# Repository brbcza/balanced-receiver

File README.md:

# Balanced Audio Receiver

The **Balanced Audio Receiver** is a versatile, compact PCB (Printed Circuit Board) designed for DIY audio enthusiasts, particularly for use as an input stage in custom speaker projects. The design integrates a balanced XLR 3-pin input and includes an onboard 5V buck converter to provide power for additional components, making it a comprehensive solution for audio applications that require both signal processing and power management.

This board is ideal for anyone looking to build high-quality audio systems, such as home audio setups or custom speaker projects, with a focus on clean, balanced audio signal processing.

> [!NOTE]  
> The latest production files for the Balanced Audio Receiver can be downloaded from the [latest release](https://github.com/brbcza/balanced-receiver/releases/latest).  
> The [Interactive BOM](https://brbcza.github.io/balanced-receiver/balanced-receiver_ibom.html) is also available in the latest release for easier component sourcing.

## Key Futures

The Balanced Audio Receiver board incorporates several essential features to ensure high performance and flexibility:

* Fully balanced XLR input
* Diferencial THAT1240 amplifier to process incoming audio signal
* Integrated 5V buck converter to power onboard ICs and additional external electronics
* Integraded charge pump to generate -5V to power signal amplifier
* Optional 5V output to power external FAN

## Board Design and Component Sourcing

The Balanced Audio Receiver PCB is designed to be as modular and flexible as possible. It is intended for use in various custom audio systems where space, signal integrity, and power efficiency are important considerations. The generated [Bill of Materials](https://github.com/brbcza/balanced-receiver/releases/latest) from latest release will help to guide you in sourcing the components for assembly.

> **Interactive BOM**  
> The interactive BOM can be found at the following link: [Interactive BOM](https://brbcza.github.io/balanced-receiver/balanced-receiver_ibom.html).

## Contributing

I welcome any contributions to the project. If you have suggestions for improvements, bug fixes, or want to add new features, feel free to submit pull requests or open issues.

## License

The Balanced Audio Receiver is open-source hardware, licensed under the [GPLv3 License](LICENSE). Feel free to modify and adapt the design for your own use, but please attribute the original project if you distribute it.

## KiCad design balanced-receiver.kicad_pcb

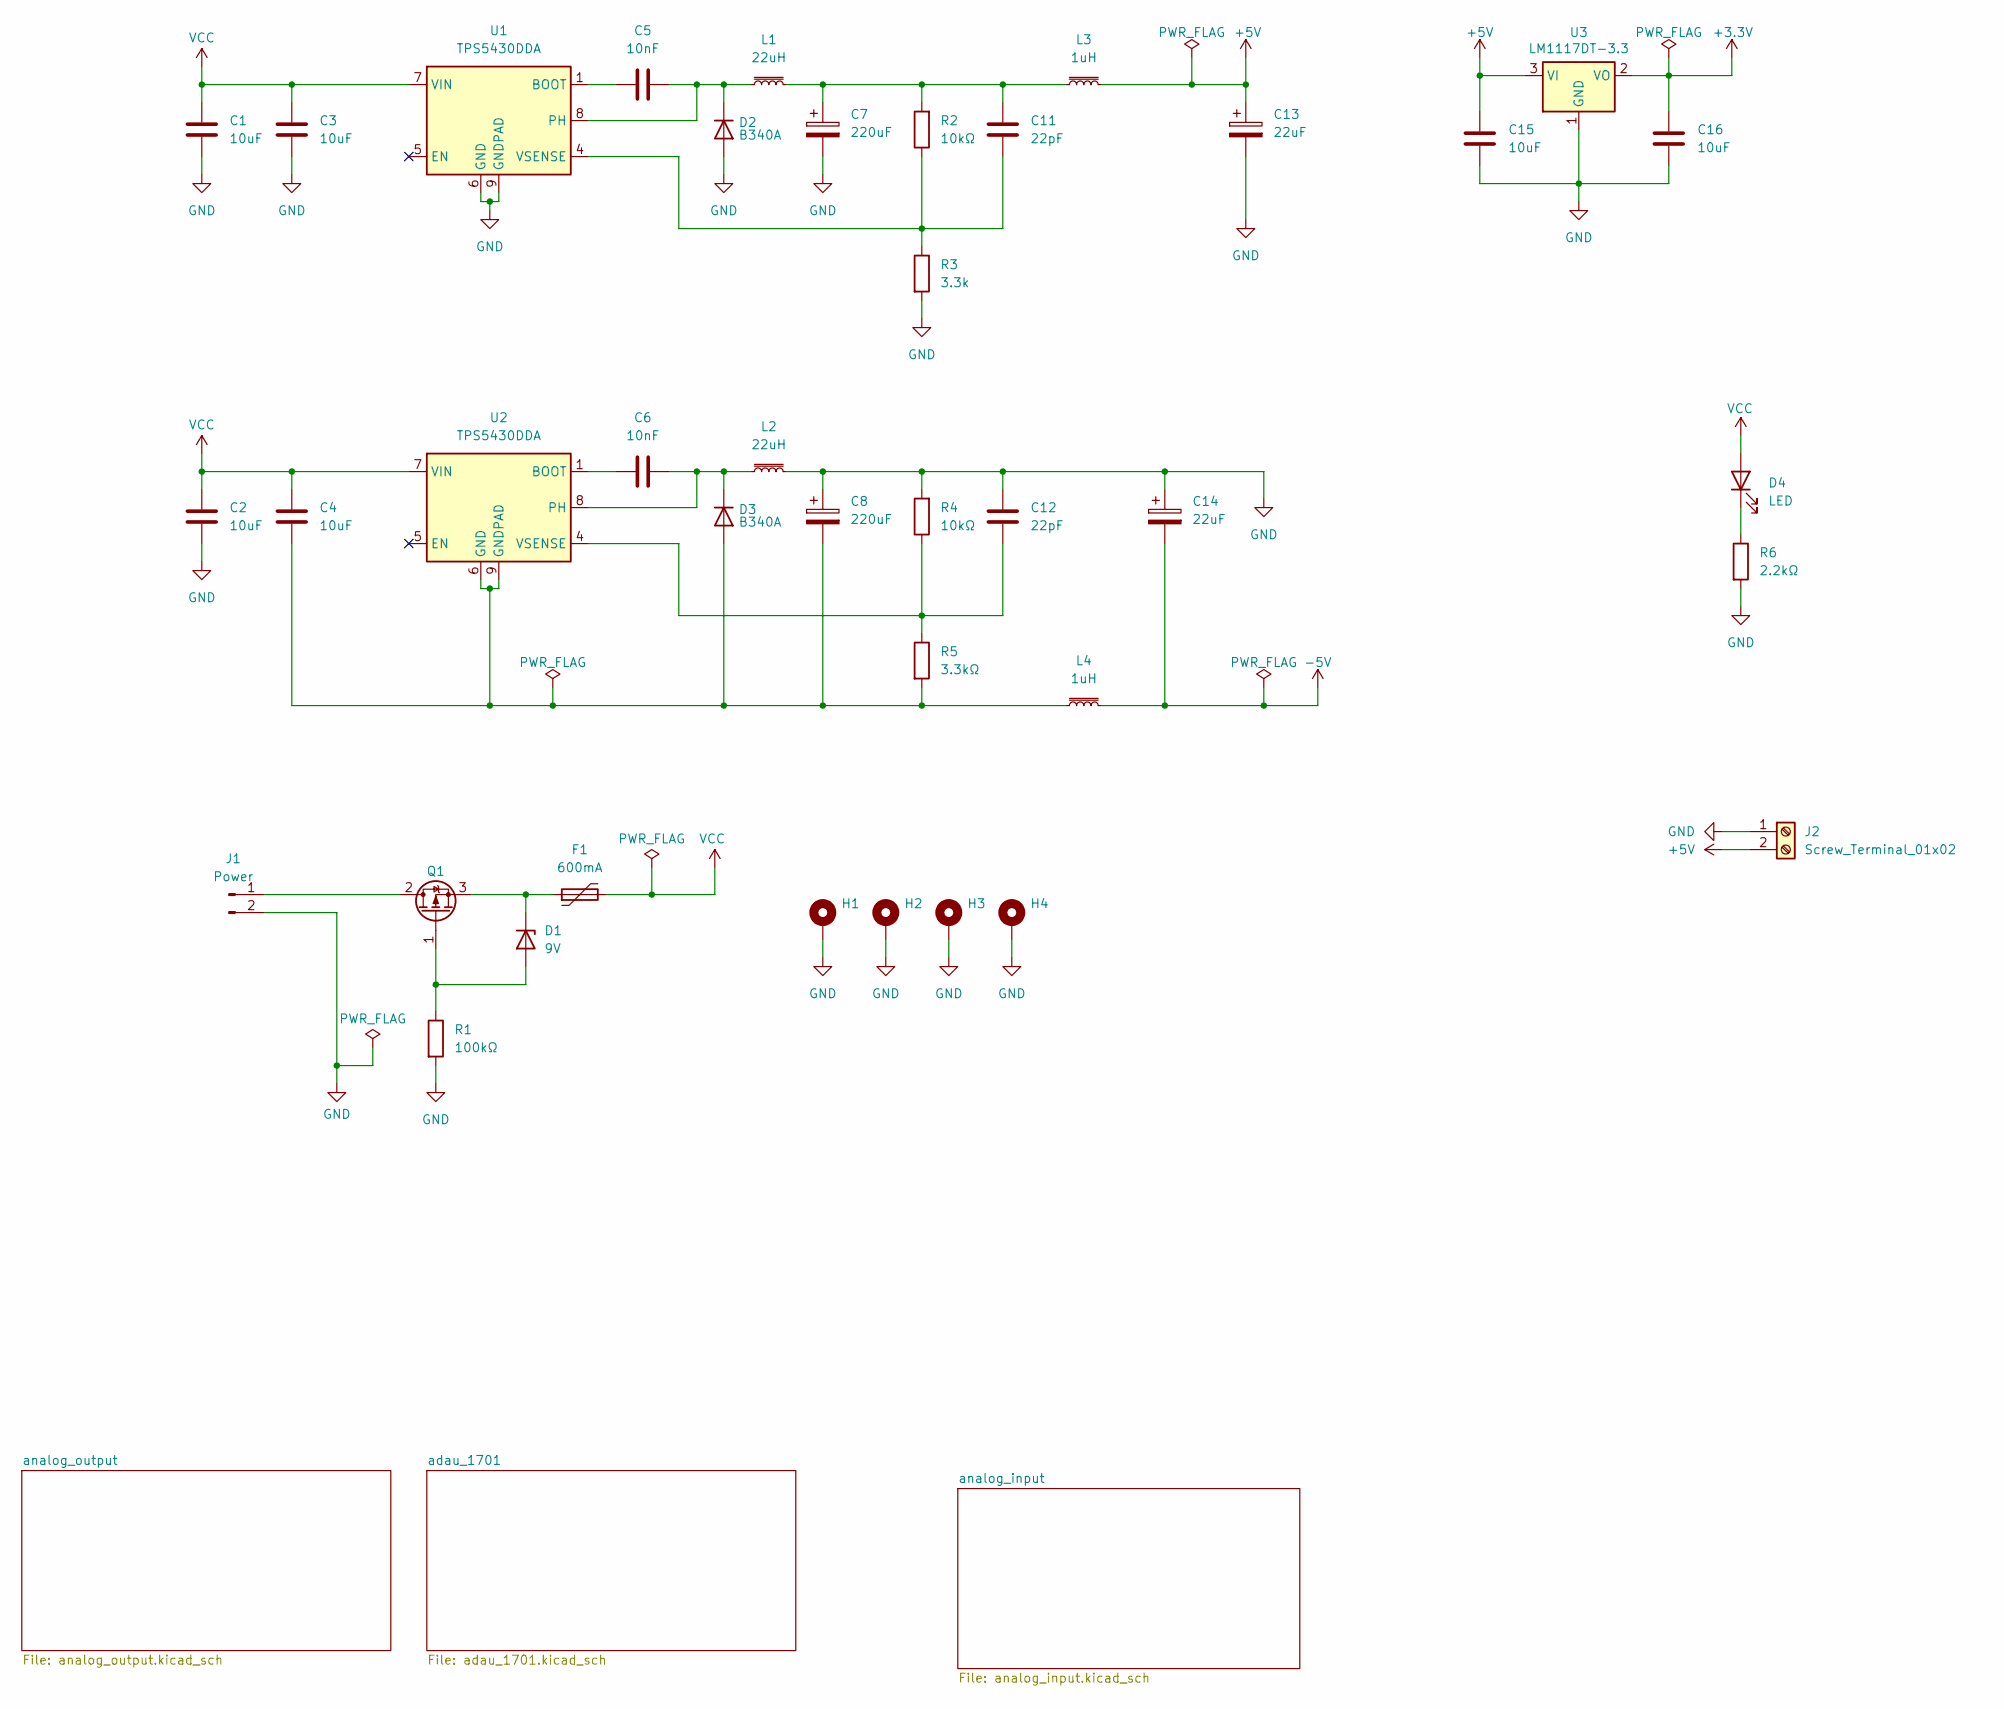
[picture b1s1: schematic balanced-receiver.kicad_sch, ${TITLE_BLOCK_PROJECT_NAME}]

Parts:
C1, C2, C3, C4, C15, C16: 10uF; C_0805_2012Metric_Pad1.18x1.45mm_HandSolder
C5, C6: 10nF; C_0805_2012Metric_Pad1.18x1.45mm_HandSolder
C7, C8: 220uF; CP_Elec_6.3x7.7
C11, C12: 22pF; C_0805_2012Metric_Pad1.18x1.45mm_HandSolder
C13, C14: 22uF; CP_Elec_4x5.4
D1: 9V; D_SOD-123; LCSC C5182291
D2, D3: B340A; D_SMA_Handsoldering
D4: LED; LED_0805_2012Metric_Pad1.15x1.40mm_HandSolder
F1: 600mA; Fuse_1812_4532Metric_Pad1.30x3.40mm_HandSolder; LCSC C135357
H1, H2, H3, H4: MountingHole_Pad_MP; MountingHole_2.2mm_M2_DIN965_Pad_TopBottom
J1: Power; JST_XH_B2B-XH-A_1x02_P2.50mm_Vertical
J2: Screw_Terminal_01x02; JST_XH_B2B-XH-AM_1x02_P2.50mm_Vertical
L1, L2: 22uH; L_APV_ANR6028
L3, L4: 1uH; L_APV_APH0420
Q1: Q_PMOS_GDS; SOT-223-3_TabPin2; LCSC SOT-23
R1: 100kΩ; R_0805_2012Metric_Pad1.20x1.40mm_HandSolder
R2, R4: 10kΩ; R_0805_2012Metric_Pad1.20x1.40mm_HandSolder
R3: 3.3k; R_0805_2012Metric_Pad1.20x1.40mm_HandSolder
R5: 3.3kΩ; R_0805_2012Metric_Pad1.20x1.40mm_HandSolder
R6: 2.2kΩ; R_0805_2012Metric_Pad1.20x1.40mm_HandSolder
U1, U2: TPS5430DDA; TI_SO-PowerPAD-8
U3: LM1117DT-3.3; SOT-223-3_TabPin2

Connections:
+3.3V: C16.2, U3.2 (VO); also elsewhere on the board
+5V: C13.1, C15.2, J2.2, L3.2, U3.3 (VI); also elsewhere on the board
-5V: C14.2, L4.2; also elsewhere on the board
GND: C1.2, C2.2, C3.2, C7.2, C8.1, C12.1, C13.2, C14.1, C15.1, C16.1, D2.2 (A), H1.MP, H2.MP, H3.MP, H4.MP, J1.2, J2.1, L2.2, R1.2, R3.2, R4.2, R6.2, U1.6 (GND), U1.9 (GNDPAD), U3.1 (GND); also elsewhere on the board
unnamed: C7.1, C11.1, L1.2, L3.1, R2.2
unnamed: D1.2 (A), Q1.1 (G), R1.1
unnamed: D1.1 (K), F1.1, Q1.3 (S)
unnamed: C5.2, D2.1 (K), L1.1, U1.8 (PH)
unnamed: C4.2, C8.2, D3.2 (A), L4.1, R5.2, U2.6 (GND), U2.9 (GNDPAD)
unnamed: C6.2, D3.1 (K), L2.1, U2.8 (PH)
unnamed: D4.1 (K), R6.1
unnamed: J1.1, Q1.2 (D)
unnamed: C5.1, U1.1 (BOOT)
unnamed: C11.2, R2.1, R3.1, U1.4 (VSENSE)
unnamed: C6.1, U2.1 (BOOT)
unnamed: C12.2, R4.1, R5.1, U2.4 (VSENSE)
VCC: C1.1, C2.1, C3.1, C4.1, D4.2 (A), F1.2, U1.7 (VIN), U2.7 (VIN); also elsewhere on the board

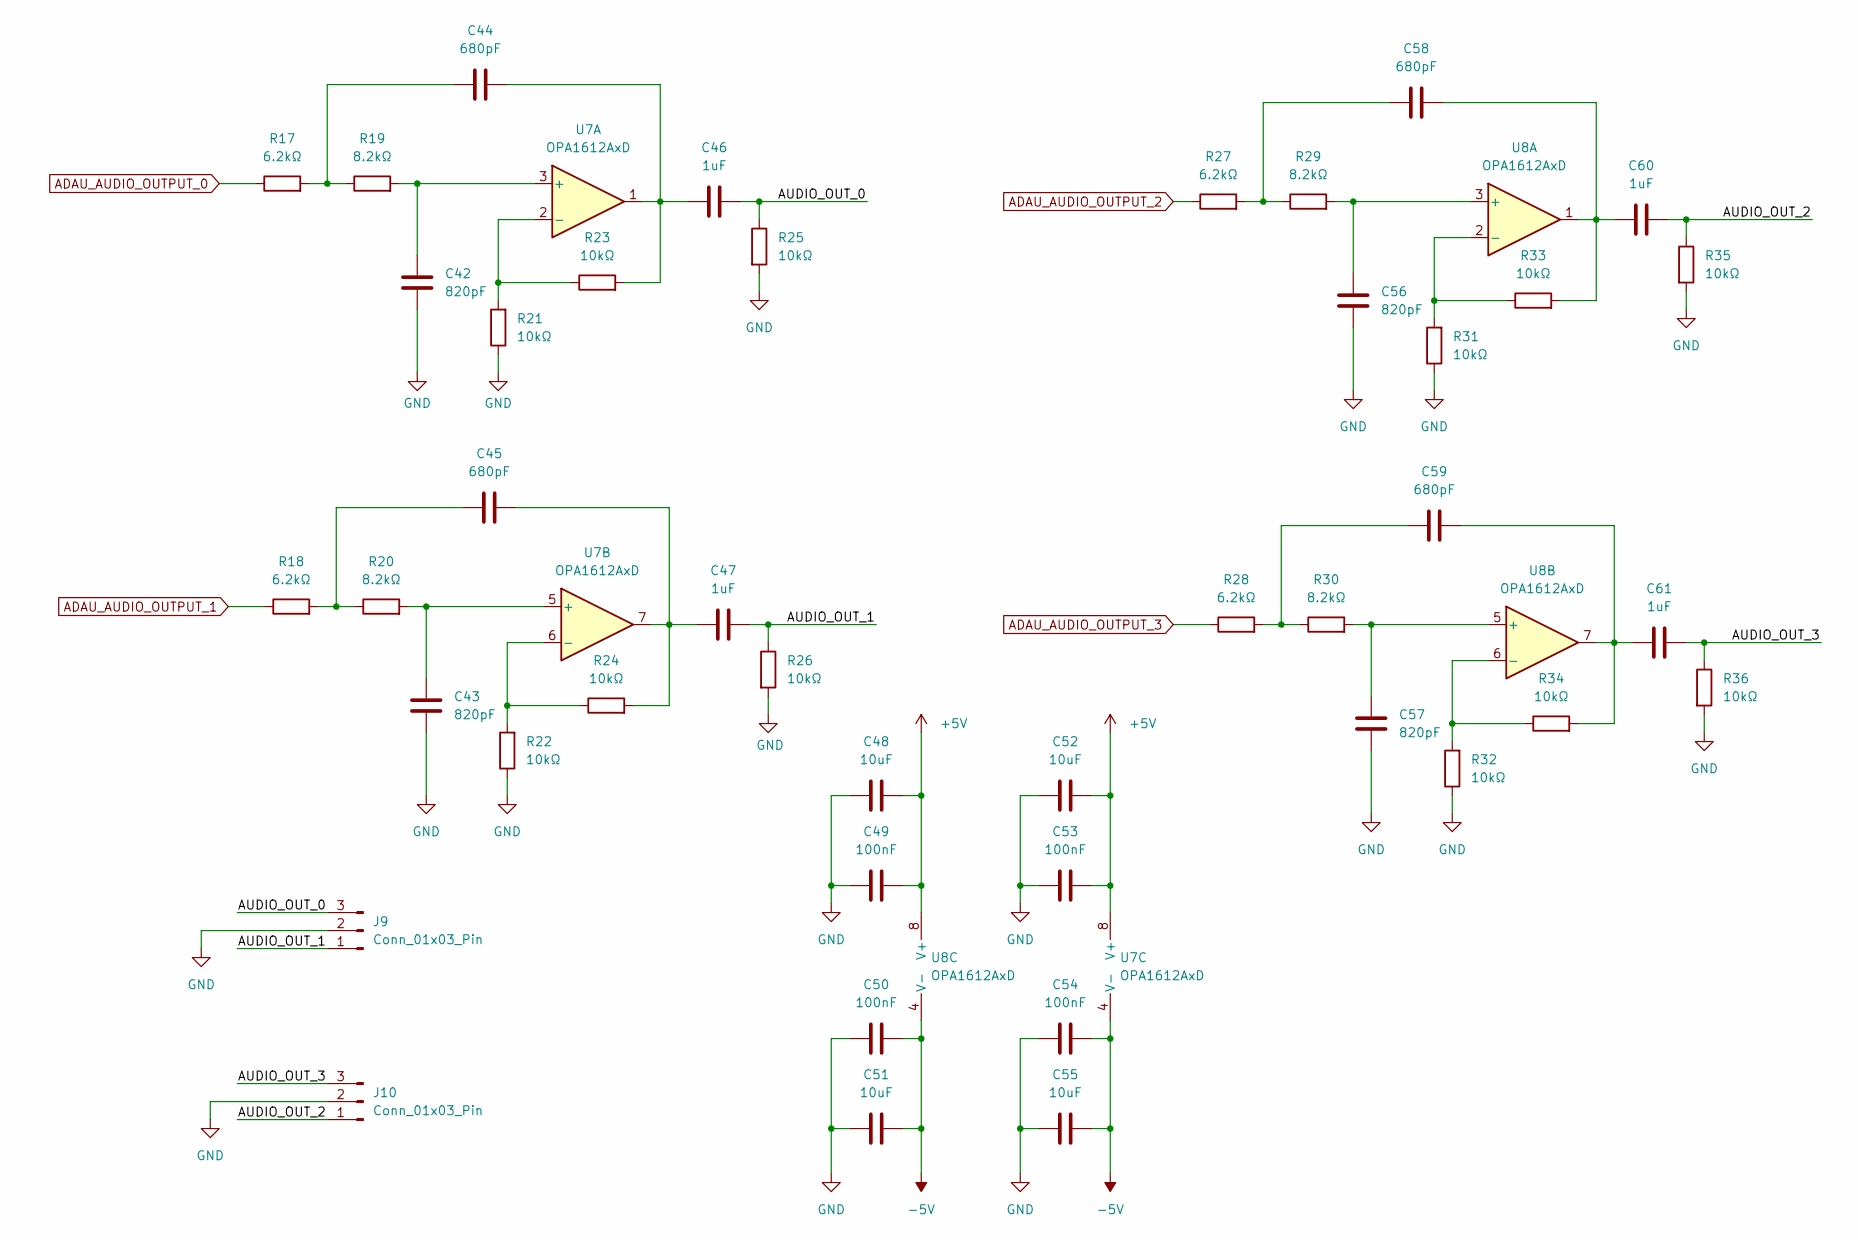
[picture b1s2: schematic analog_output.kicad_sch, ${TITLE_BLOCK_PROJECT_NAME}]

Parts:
C42, C43, C56, C57: 820pF; C_0805_2012Metric_Pad1.18x1.45mm_HandSolder
C44, C45, C58, C59: 680pF; C_0805_2012Metric_Pad1.18x1.45mm_HandSolder
C46, C47, C60, C61: 1uF; C_0805_2012Metric_Pad1.18x1.45mm_HandSolder
C48, C51, C52, C55: 10uF; C_0805_2012Metric_Pad1.18x1.45mm_HandSolder
C49, C50, C53, C54: 100nF; C_0805_2012Metric_Pad1.18x1.45mm_HandSolder
J9, J10: Conn_01x03_Pin; JST_XH_B3B-XH-A_1x03_P2.50mm_Vertical
R17, R18, R27, R28: 6.2kΩ; R_0805_2012Metric_Pad1.20x1.40mm_HandSolder
R19, R20, R29, R30: 8.2kΩ; R_0805_2012Metric_Pad1.20x1.40mm_HandSolder
R21, R22, R23, R24, R25, R26, R31, R32, R33, R34, R35, R36: 10kΩ; R_0805_2012Metric_Pad1.20x1.40mm_HandSolder
U7, U8: OPA1612AxD; SOIC-8_3.9x4.9mm_P1.27mm

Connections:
+5V: C48.1, C49.1, C52.1, C53.1, U7.8 (V+), U8.8 (V+); also elsewhere on the board
-5V: C50.1, C51.1, C54.1, C55.1, U7.4 (V-), U8.4 (V-); also elsewhere on the board
/analog_output/AUDIO_OUT_0: C46.2, J9.3, R25.1
/analog_output/AUDIO_OUT_1: C47.2, J9.1, R26.1
/analog_output/AUDIO_OUT_2: C60.2, J10.1, R35.1
/analog_output/AUDIO_OUT_3: C61.2, J10.3, R36.1
ADAU_AUDIO_OUTPUT_0: R17.1; also elsewhere on the board
ADAU_AUDIO_OUTPUT_1: R18.1; also elsewhere on the board
ADAU_AUDIO_OUTPUT_2: R27.1; also elsewhere on the board
ADAU_AUDIO_OUTPUT_3: R28.1; also elsewhere on the board
GND: C42.1, C43.1, C48.2, C49.2, C50.2, C51.2, C52.2, C53.2, C54.2, C55.2, C56.1, C57.1, J9.2, J10.2, R21.1, R22.1, R25.2, R26.2, R31.1, R32.1, R35.2, R36.2; also elsewhere on the board
unnamed: C44.1, R17.2, R19.1
unnamed: C44.2, C46.1, R23.2, U7.1
unnamed: C45.1, R18.2, R20.1
unnamed: C45.2, C47.1, R24.2, U7.7
unnamed: C58.1, R27.2, R29.1
unnamed: C58.2, C60.1, R33.2, U8.1
unnamed: C59.1, R28.2, R30.1
unnamed: C59.2, C61.1, R34.2, U8.7
unnamed: C42.2, R19.2, U7.3 (+)
unnamed: R21.2, R23.1, U7.2 (-)
unnamed: C43.2, R20.2, U7.5 (+)
unnamed: R22.2, R24.1, U7.6 (-)
unnamed: C56.2, R29.2, U8.3 (+)
unnamed: R31.2, R33.1, U8.2 (-)
unnamed: C57.2, R30.2, U8.5 (+)
unnamed: R32.2, R34.1, U8.6 (-)

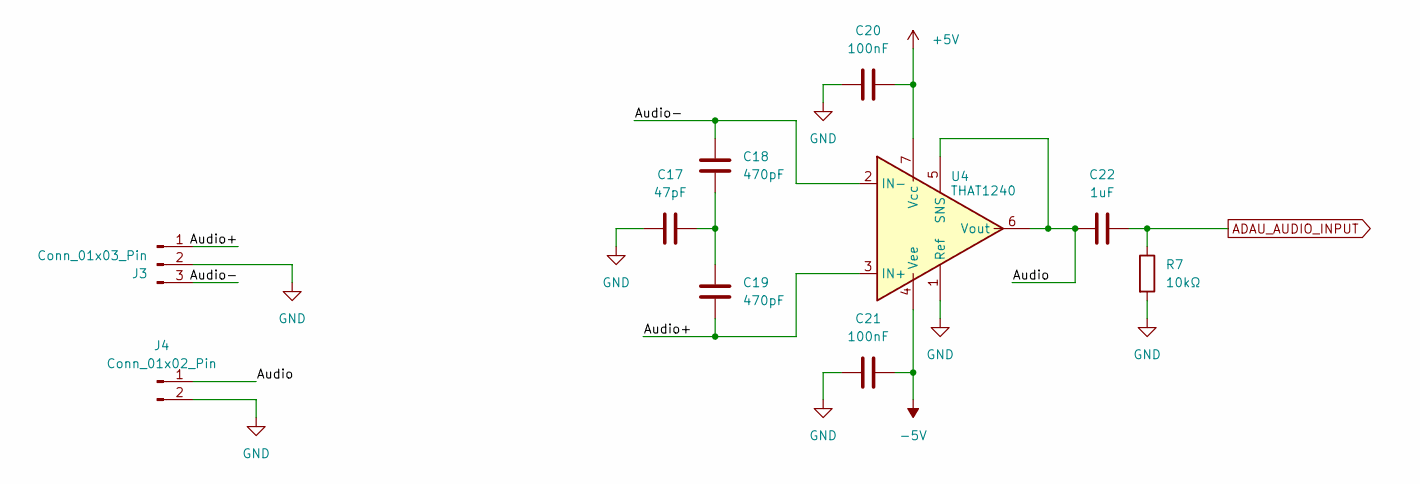
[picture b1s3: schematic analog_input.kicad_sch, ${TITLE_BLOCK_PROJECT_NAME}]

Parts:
C17: 47pF; C_0805_2012Metric_Pad1.18x1.45mm_HandSolder
C18, C19: 470pF; C_0805_2012Metric_Pad1.18x1.45mm_HandSolder
C20, C21: 100nF; C_0805_2012Metric_Pad1.18x1.45mm_HandSolder
C22: 1uF; C_0805_2012Metric_Pad1.18x1.45mm_HandSolder
J3: Conn_01x03_Pin; JST_XH_B3B-XH-A_1x03_P2.50mm_Vertical
J4: Conn_01x02_Pin; JST_XH_B2B-XH-A_1x02_P2.50mm_Vertical
R7: 10kΩ; R_0805_2012Metric_Pad1.20x1.40mm_HandSolder
U4: THAT1240; SOIC-8_3.9x4.9mm_P1.27mm

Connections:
+5V: C20.1, U4.7 (Vcc); also elsewhere on the board
-5V: C21.1, U4.4 (Vee); also elsewhere on the board
/analog_input/Audio: C22.1, J4.1, U4.5 (SNS), U4.6 (Vout)
/analog_input/Audio+: C19.2, J3.1, U4.3 (IN+)
/analog_input/Audio-: C18.1, J3.3, U4.2 (IN-)
ADAU_AUDIO_INPUT: C22.2, R7.1; also elsewhere on the board
GND: C17.1, C20.2, C21.2, J3.2, J4.2, R7.2, U4.1 (Ref); also elsewhere on the board
unnamed: C17.2, C18.2, C19.1

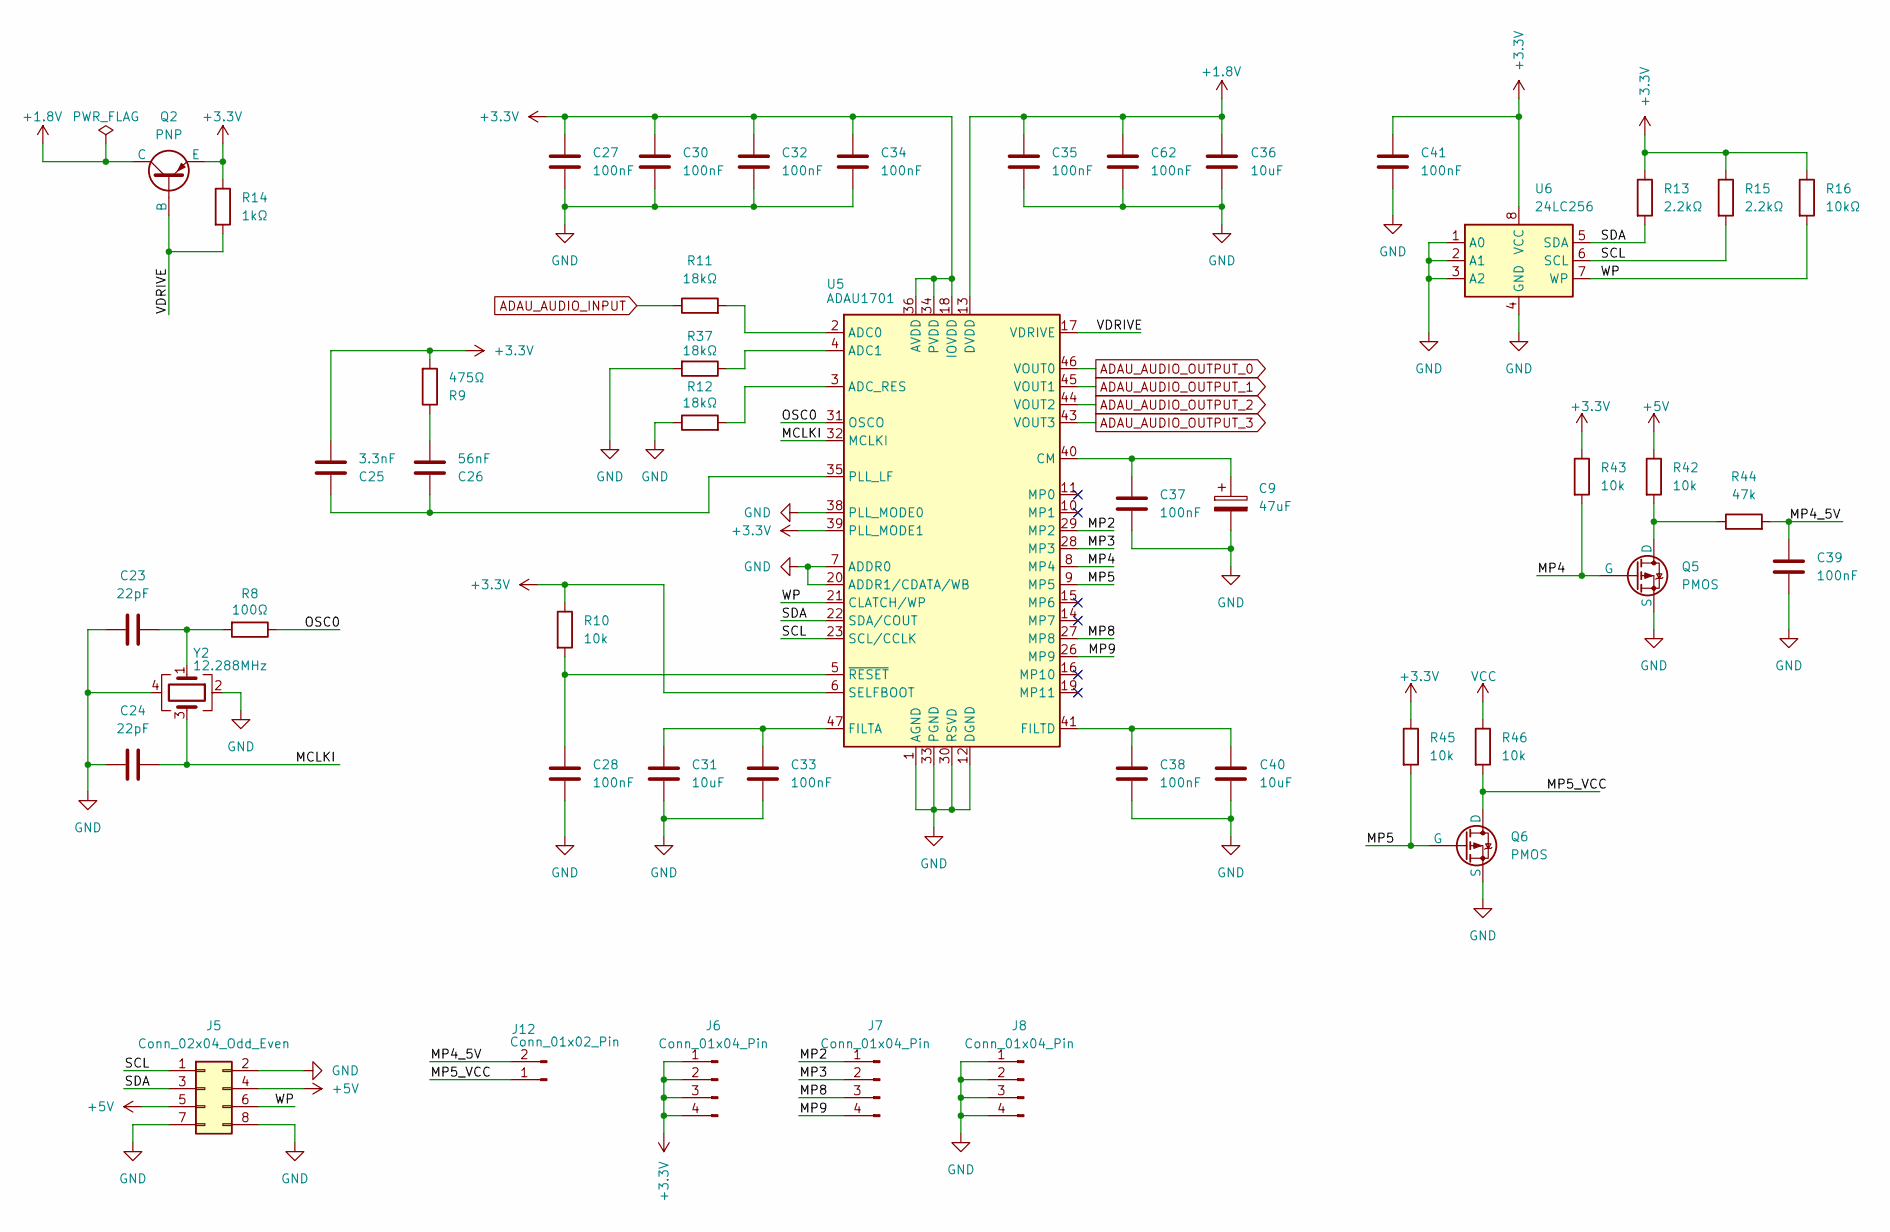
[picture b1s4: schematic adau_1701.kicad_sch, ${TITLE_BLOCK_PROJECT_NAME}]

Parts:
C9: 47uF; CP_Elec_5x5.4
C23, C24: 22pF; C_0805_2012Metric_Pad1.18x1.45mm_HandSolder
C25: 3.3nF; C_0805_2012Metric_Pad1.18x1.45mm_HandSolder
C26: 56nF; C_0805_2012Metric_Pad1.18x1.45mm_HandSolder
C27, C28, C30, C32, C33, C34, C35, C37, C38, C39, C41, C62: 100nF; C_0805_2012Metric_Pad1.18x1.45mm_HandSolder
C31, C36, C40: 10uF; C_0805_2012Metric_Pad1.18x1.45mm_HandSolder
J5: Conn_02x04_Odd_Even; PinHeader_2x04_P2.54mm_Vertical
J6, J7, J8: Conn_01x04_Pin; PinHeader_1x04_P2.54mm_Vertical
J12: Conn_01x02_Pin; PinHeader_1x02_P2.54mm_Vertical
Q2: PNP; SOT-23
Q5, Q6: PMOS; SOT-23
R8: 100Ω; R_0805_2012Metric_Pad1.20x1.40mm_HandSolder
R9: 475Ω; R_0805_2012Metric_Pad1.20x1.40mm_HandSolder
R10, R42, R43, R45, R46: 10k; R_0805_2012Metric_Pad1.20x1.40mm_HandSolder
R11, R12, R37: 18kΩ; R_0805_2012Metric_Pad1.20x1.40mm_HandSolder
R13, R15: 2.2kΩ; R_0805_2012Metric_Pad1.20x1.40mm_HandSolder
R14: 1kΩ; R_0805_2012Metric_Pad1.20x1.40mm_HandSolder
R16: 10kΩ; R_0805_2012Metric_Pad1.20x1.40mm_HandSolder
R44: 47k; R_0805_2012Metric_Pad1.20x1.40mm_HandSolder
U5: ADAU1701; LQFP-48_7x7mm_P0.5mm
U6: 24LC256; SOIC-8_3.9x4.9mm_P1.27mm
Y2: 12.288MHz; Crystal_SMD_3225-4Pin_3.2x2.5mm

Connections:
+1.8V: C35.2, C36.2, C62.2, Q2.1 (C), U5.13 (DVDD), U5.24 (DVDD)
+3.3V: C25.1, C27.2, C30.2, C32.2, C34.2, C41.1, J6.1, J6.2, J6.3, J6.4, Q2.3 (E), R9.2, R10.1, R13.1, R14.1, R15.1, R16.1, R43.1, R45.1, U5.6 (SELFBOOT), U5.18 (IOVDD), U5.34 (PVDD), U5.36 (AVDD), U5.39 (PLL_MODE1), U5.48 (AVDD), U6.8 (VCC); also elsewhere on the board
+5V: J5.4, J5.5, R42.1; also elsewhere on the board
/adau_1701/MCLKI: C24.2, U5.32 (MCLKI), Y2.3
/adau_1701/MP2: J7.1, U5.29 (MP2)
/adau_1701/MP3: J7.2, U5.28 (MP3)
/adau_1701/MP4: Q5.2 (G), R43.2, U5.8 (MP4)
/adau_1701/MP4_5V: C39.2, J12.2, R44.2
/adau_1701/MP5: Q6.2 (G), R45.2, U5.9 (MP5)
/adau_1701/MP5_VCC: J12.1, Q6.1 (D), R46.2
/adau_1701/MP8: J7.3, U5.27 (MP8)
/adau_1701/MP9: J7.4, U5.26 (MP9)
/adau_1701/OSC0: R8.1, U5.31 (OSCO)
/adau_1701/SCL: J5.1, R15.2, U5.23 (SCL/CCLK), U6.6 (SCL)
/adau_1701/SDA: J5.3, R13.2, U5.22 (SDA/COUT), U6.5 (SDA)
/adau_1701/VDRIVE: Q2.2 (B), R14.2, U5.17 (VDRIVE)
/adau_1701/WP: J5.6, R16.2, U5.21 (CLATCH/WP), U6.7 (WP)
ADAU_AUDIO_INPUT: R11.1; also elsewhere on the board
ADAU_AUDIO_OUTPUT_0: U5.46 (VOUT0); also elsewhere on the board
ADAU_AUDIO_OUTPUT_1: U5.45 (VOUT1); also elsewhere on the board
ADAU_AUDIO_OUTPUT_2: U5.44 (VOUT2); also elsewhere on the board
ADAU_AUDIO_OUTPUT_3: U5.43 (VOUT3); also elsewhere on the board
GND: C9.2, C23.1, C24.1, C27.1, C28.1, C30.1, C31.1, C32.1, C33.1, C34.1, C35.1, C36.1, C37.1, C38.1, C39.1, C40.1, C41.2, C62.1, J5.2, J5.7, J5.8, J8.1, J8.2, J8.3, J8.4, Q5.3 (S), Q6.3 (S), R12.1, R37.2, U5.1 (AGND), U5.7 (ADDR0), U5.12 (DGND), U5.20 (ADDR1/CDATA/WB), U5.25 (DGND), U5.30 (RSVD), U5.33 (PGND), U5.37 (AGND), U5.38 (PLL_MODE0), U5.42 (AGND), U6.1 (A0), U6.2 (A1), U6.3 (A2), U6.4 (GND), Y2.2, Y2.4; also elsewhere on the board
unnamed: C23.2, R8.2, Y2.1
unnamed: C26.1, R9.1
unnamed: Q5.1 (D), R42.2, R44.1
unnamed: R11.2, U5.2 (ADC0)
unnamed: R37.1, U5.4 (ADC1)
unnamed: R12.2, U5.3 (ADC_RES)
unnamed: C9.1, C37.2, U5.40 (CM)
unnamed: C31.2, C33.2, U5.47 (FILTA)
unnamed: C38.2, C40.2, U5.41 (FILTD)
unnamed: C25.2, C26.2, U5.35 (PLL_LF)
unnamed: C28.2, R10.2, U5.5 (~RESET)
VCC: R46.1; also elsewhere on the board

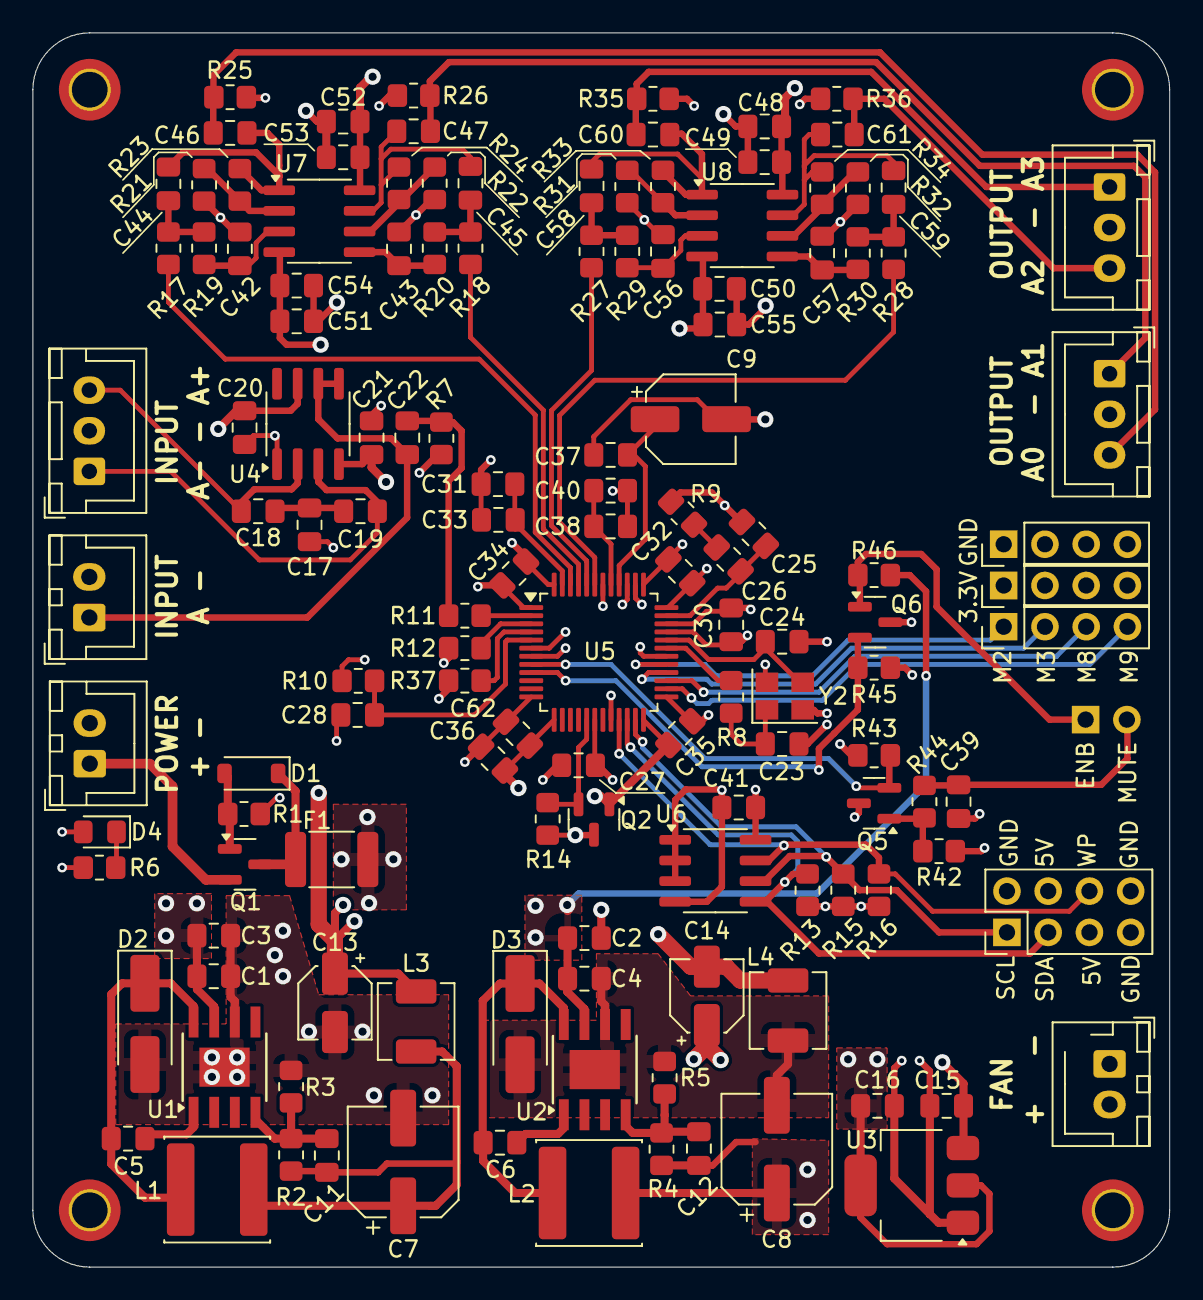
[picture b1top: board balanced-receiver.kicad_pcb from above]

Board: 4 copper layers, 70.0 x 76.0 mm, 139 parts (1 on the bottom side), 72 nets.

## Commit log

2025-02-02 Added pipeline workflow
2025-02-02 Added release workflow
2025-02-03 Added DRC pipeline action
2025-02-03 Resolved DRC errors
2025-02-03 Added release action
2025-02-03 Foxed wrong variables inside action files
2025-02-03 Execute release action only on selected branches
2025-02-04 Added pages action
2025-02-04 Updated README file
2025-02-05 Added local component library
2025-02-05 Fixed DRC and ERC errors
2025-02-05 Added link to IBOM
2025-02-05 Changed date generation script
2025-03-12 Added analog schemas
2025-03-22 WIP: Converting to schematic
2025-03-23 Update CI pipeline to use kicad/kicad:9.0 for ERC and DRC tests
2025-03-23 Update workflows and configurations for balanced-receiver project
2025-03-23 Update release workflow and date format; add installation script for kikit dependencies
2025-03-23 Update CI workflows to use ghcr.io/inti-cmnb/kicad9_auto_full
2025-03-23 Adjust via positions in PCB layout
2025-05-04 Completed PCB
